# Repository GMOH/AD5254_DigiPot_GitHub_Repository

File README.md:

AD5254_DigiPot_GitHub_Repository
================================

    AD525X Digital potentiometer code.
    
    More documentation can be found at http://familia-herrera.com/wordpress/archives/576
    Copyright (C) 2014  Guillermo Herrera

    This program is free software: you can redistribute it and/or modify
    it under the terms of the GNU General Public License as published by
    the Free Software Foundation, either version 3 of the License, or
    (at your option) any later version.

    This program is distributed in the hope that it will be useful,
    but WITHOUT ANY WARRANTY; without even the implied warranty of
    MERCHANTABILITY or FITNESS FOR A PARTICULAR PURPOSE.  See the
    GNU General Public License for more details.

    You should have received a copy of the GNU General Public License
    along with this program.  If not, see <http://www.gnu.org/licenses/>.
   
Notes:
Currently the files are standalone files, fully functional.  The Goal is to make a library that can be dropped in the arduino library folder with an example on how to use the code.  (Working on it)

Any help from others is welcome

ToDo:
1. Add open hardware license to EAGLE files
2. Create *.h and *.cpp and keywords.txt files for library
3. Update Website with more details and videos

Change Log:
4/8/14  First commit, arduino code files, EAGLE board files.
4/9/14  Added license file, description to individual files

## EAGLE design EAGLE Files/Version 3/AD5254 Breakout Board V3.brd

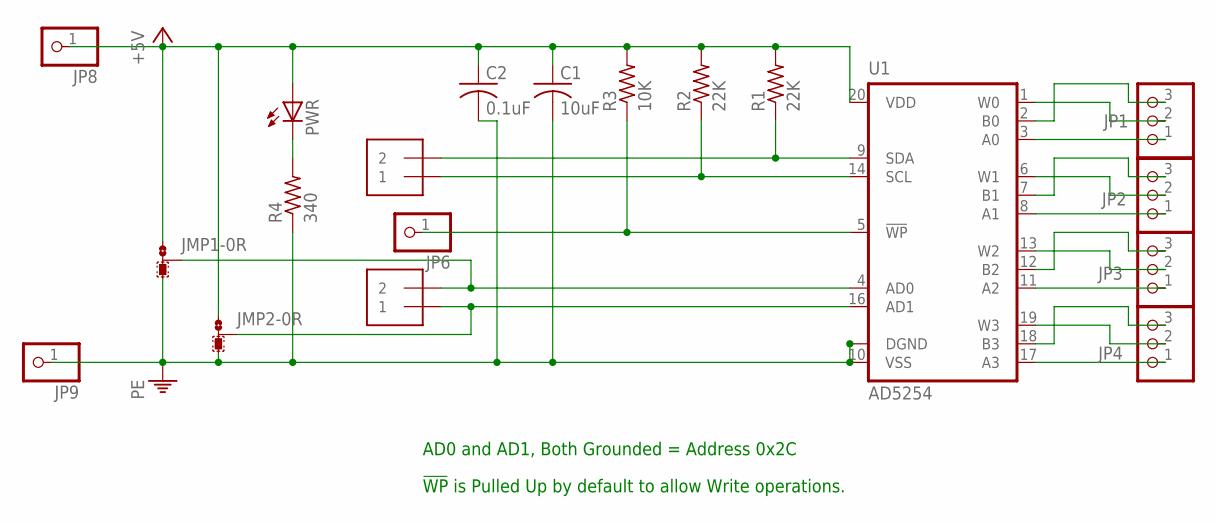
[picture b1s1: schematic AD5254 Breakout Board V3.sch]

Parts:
C1: 10uF; C0805
C2: 0.1uF; C0805
JMP1, JMP2: 0R-JUMPA; A0R-JMP
JP1, JP2, JP3, JP4: PINHD-1X3CB; 1X03-CLEANBIG
JP5, JP7: PINHD-1X2GD; 1X02-CLEANBIG
JP6, JP8, JP9: PINHD-1X1CB; 1X01-CLEANBIG
PWR: LED3MM
R1, R2: 22K; M0805
R3: 10K; M0805
R4: 340; M0805
U1: AD5254

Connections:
+5V: C1.1, C2.1, JMP1.1, JMP2.1, JP8.1, PWR.A, R1.2, R2.2, R3.2, U1.20 (VDD)
GND: C1.2, C2.2, JMP1.3, JMP2.3, JP9.1, R4.1, U1.10 (VSS), U1.15 (DGND)
unnamed: JP1.2, U1.1 (W0)
unnamed: JP6.1, R3.1, U1.5 (!WP)
unnamed: JP1.3, U1.2 (B0)
unnamed: JP1.1, U1.3 (A0)
unnamed: JP2.1, U1.8 (A1)
unnamed: JP3.1, U1.11 (A2)
unnamed: JP4.1, U1.17 (A3)
unnamed: JP4.3, U1.18 (B3)
unnamed: JP4.2, U1.19 (W3)
unnamed: JP2.3, U1.7 (B1)
unnamed: JP2.2, U1.6 (W1)
unnamed: JP3.3, U1.12 (B2)
unnamed: JP3.2, U1.13 (W2)
unnamed: JP5.2, R1.1, U1.9 (SDA)
unnamed: JP5.1, R2.1, U1.14 (SCL)
unnamed: JMP1.2, JP7.2, U1.4 (AD0)
unnamed: JMP2.2, JP7.1, U1.16 (AD1)
unnamed: PWR.K (C), R4.2

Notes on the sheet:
AD0 and AD1, Both Grounded = Address 0x2C
!WP! is Pulled Up by default to allow Write operations.

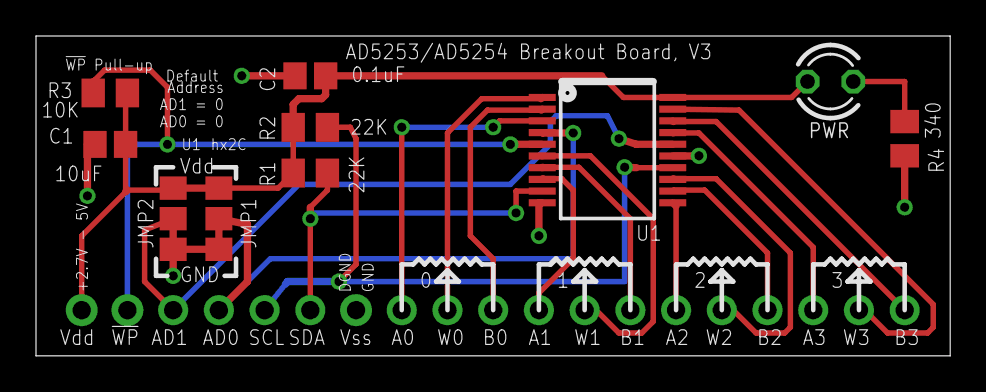
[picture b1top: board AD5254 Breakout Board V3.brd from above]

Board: 2 copper layers, 50.8 x 17.8 mm, 19 parts (0 on the bottom side), 20 nets.

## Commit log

2014-04-08 Initial Files
    First files, more info at:
    http://familia-herrera.com/wordpress/archives/576
2014-04-09 Added license and more description to code
    Added license and more description to the code files.
    Still need to create a library. Currently all files have all the
    functions.
2014-04-11 Deleted a file
    File used for reference was deleted, links to the resources used for
    this code have been listed in the info website.
